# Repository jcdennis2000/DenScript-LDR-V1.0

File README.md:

# DenScript-LDR-V1.0

The DenScript LDR (Light Dependant Resistor) Module is a variable resistor that adjusts its resistance depending on the amount of light that is hitting its surface. This is housed in a convenient package that allows it to be easily attached to projects, with our DenScript colour coded headers to make wiring far easier! Simply connect the RED pin to positive voltage (VCC), the BLACK pin to negative voltage (GND) and the GREEN pin to an input pin on your micro controller or development board!

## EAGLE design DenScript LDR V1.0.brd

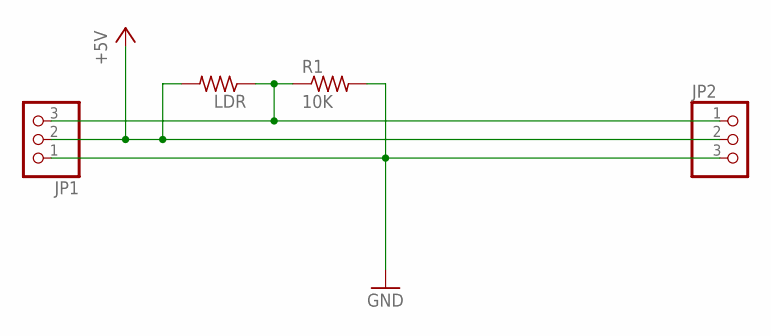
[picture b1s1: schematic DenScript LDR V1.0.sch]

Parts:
JP1, JP2: PINHD-1X3; 1X03
LDR: R-US_0204/5; 0204/5
R1: 10K; R0603

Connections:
+5V: JP1.2, JP2.2, LDR.2
GND: JP1.1, JP2.3, R1.2
unnamed: JP1.3, JP2.1, LDR.1, R1.1

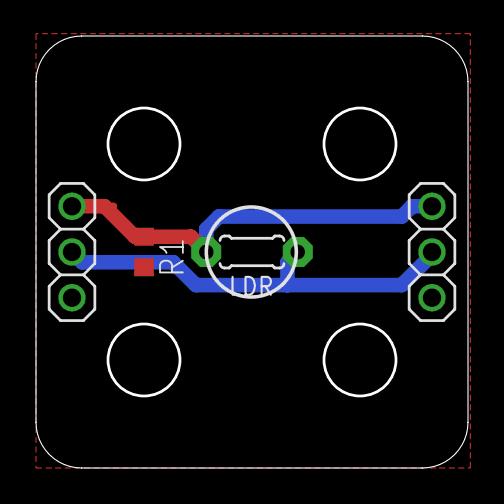
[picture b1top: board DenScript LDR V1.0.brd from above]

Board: 2 copper layers, 23.8 x 23.8 mm, 4 parts (0 on the bottom side), 3 nets.

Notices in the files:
DenScript LDR V1.0.brd:
Dennistries Ltd (c) 2019
